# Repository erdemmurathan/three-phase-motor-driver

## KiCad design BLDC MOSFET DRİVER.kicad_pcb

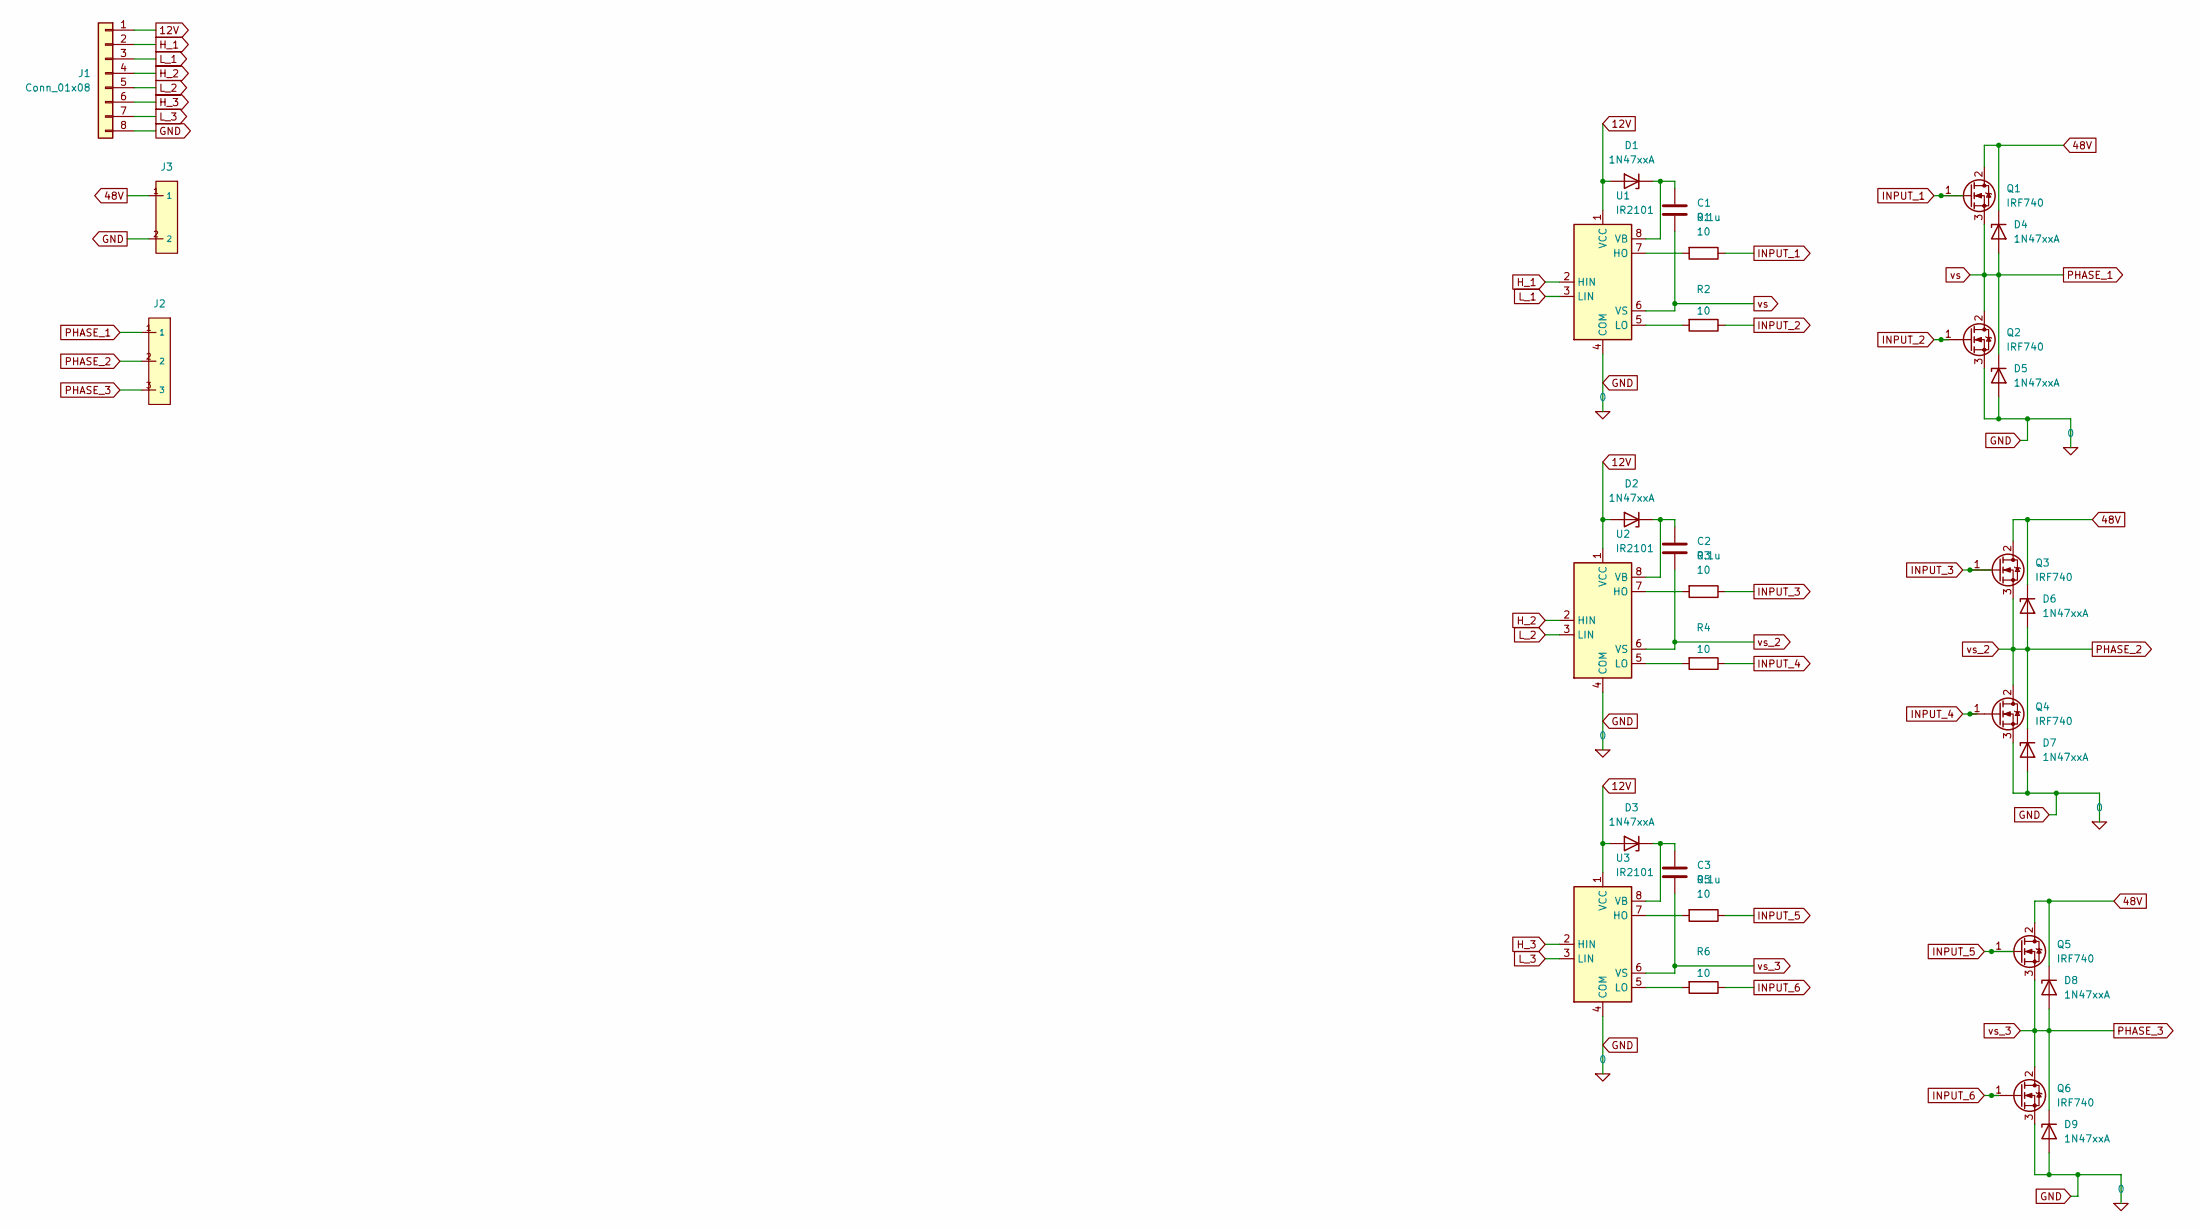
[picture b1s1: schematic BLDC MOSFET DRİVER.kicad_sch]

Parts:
C1, C2, C3: 0.1u; CP_Elec_10x10
D1, D2, D3, D4, D5, D6, D7, D8, D9: 1N47xxA; D_A-405_P12.70mm_Horizontal
J1: Conn_01x08; PinSocket_1x08_P2.54mm_Vertical
J2: PhoenixContact_MCV_1,5_3-G-5.08_1x03_P5.08mm_Vertical
J3: PhoenixContact_MCV_1,5_2-G-5.08_1x02_P5.08mm_Vertical
Q1, Q2, Q3, Q4, Q5, Q6: IRF740; TO-247-3_Vertical
R1, R2, R3, R4, R5, R6: 10; R_2512_6332Metric_Pad1.40x3.35mm_HandSolder
U1, U2, U3: IR2101; SMDIP-8_W7.62mm

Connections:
12V: D1.2 (A), D2.2 (A), D3.2 (A), J1.1, U1.1 (VCC), U2.1 (VCC), U3.1 (VCC)
48V: D4.1 (K), D6.1 (K), D8.1 (K), J3.1, Q1.2 (D), Q3.2 (D), Q5.2 (D)
GND: D5.2 (A), D7.2 (A), D9.2 (A), J1.8, J3.2, Q2.3 (S), Q4.3 (S), Q6.3 (S), U1.4 (COM), U2.4 (COM), U3.4 (COM)
H_1: J1.2, U1.2 (HIN)
H_2: J1.4, U2.2 (HIN)
H_3: J1.6, U3.2 (HIN)
INPUT_1: Q1.1 (G), R1.1
INPUT_2: Q2.1 (G), R2.1
INPUT_3: Q3.1 (G), R3.1
INPUT_4: Q4.1 (G), R4.1
INPUT_5: Q5.1 (G), R5.1
INPUT_6: Q6.1 (G), R6.1
L_1: J1.3, U1.3 (LIN)
L_2: J1.5, U2.3 (LIN)
L_3: J1.7, U3.3 (LIN)
unnamed: C1.1, D1.1 (K), U1.8 (VB)
unnamed: C2.1, D2.1 (K), U2.8 (VB)
unnamed: C3.1, D3.1 (K), U3.8 (VB)
unnamed: R1.2, U1.7 (HO)
unnamed: R2.2, U1.5 (LO)
unnamed: R3.2, U2.7 (HO)
unnamed: R4.2, U2.5 (LO)
unnamed: R5.2, U3.7 (HO)
PHASE_1: C1.2, D4.2 (A), D5.1 (K), J2.1, Q1.3 (S), Q2.2 (D), U1.6 (VS)
PHASE_2: C2.2, D6.2 (A), D7.1 (K), J2.2, Q3.3 (S), Q4.2 (D), U2.6 (VS)

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
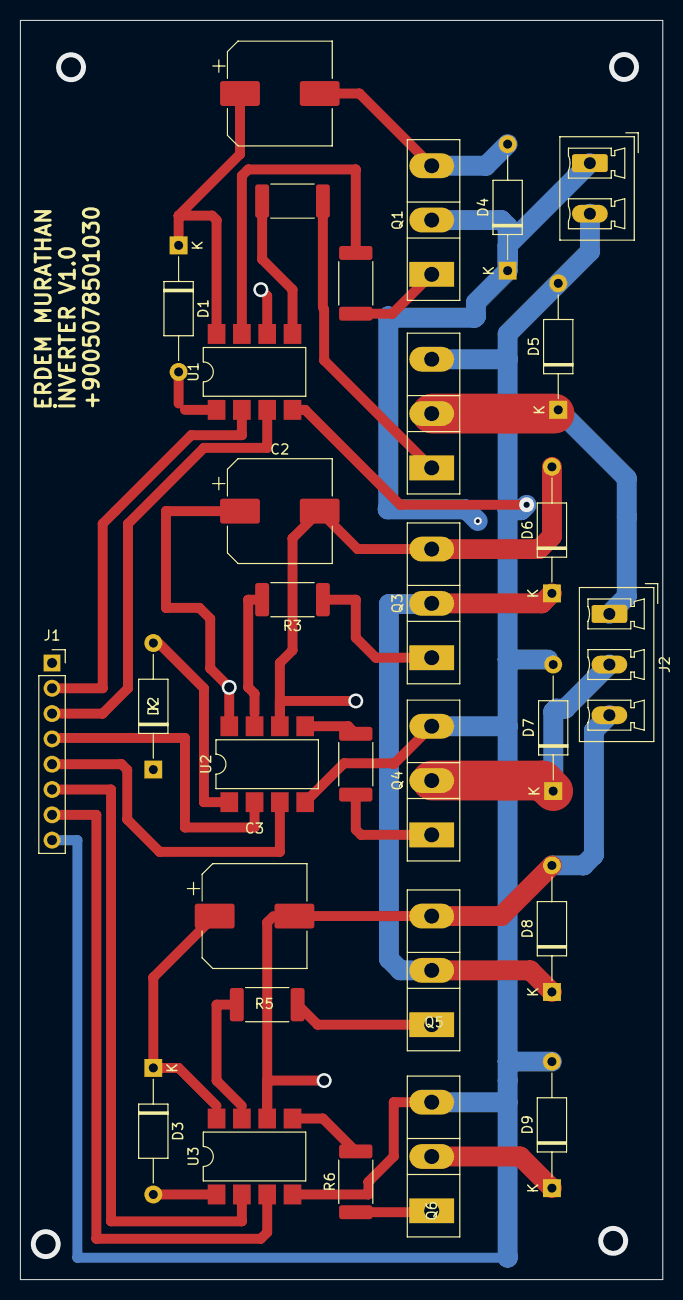
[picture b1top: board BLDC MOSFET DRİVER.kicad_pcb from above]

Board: 4 copper layers, 64.5 x 126.4 mm, 30 parts (0 on the bottom side), 26 nets.
